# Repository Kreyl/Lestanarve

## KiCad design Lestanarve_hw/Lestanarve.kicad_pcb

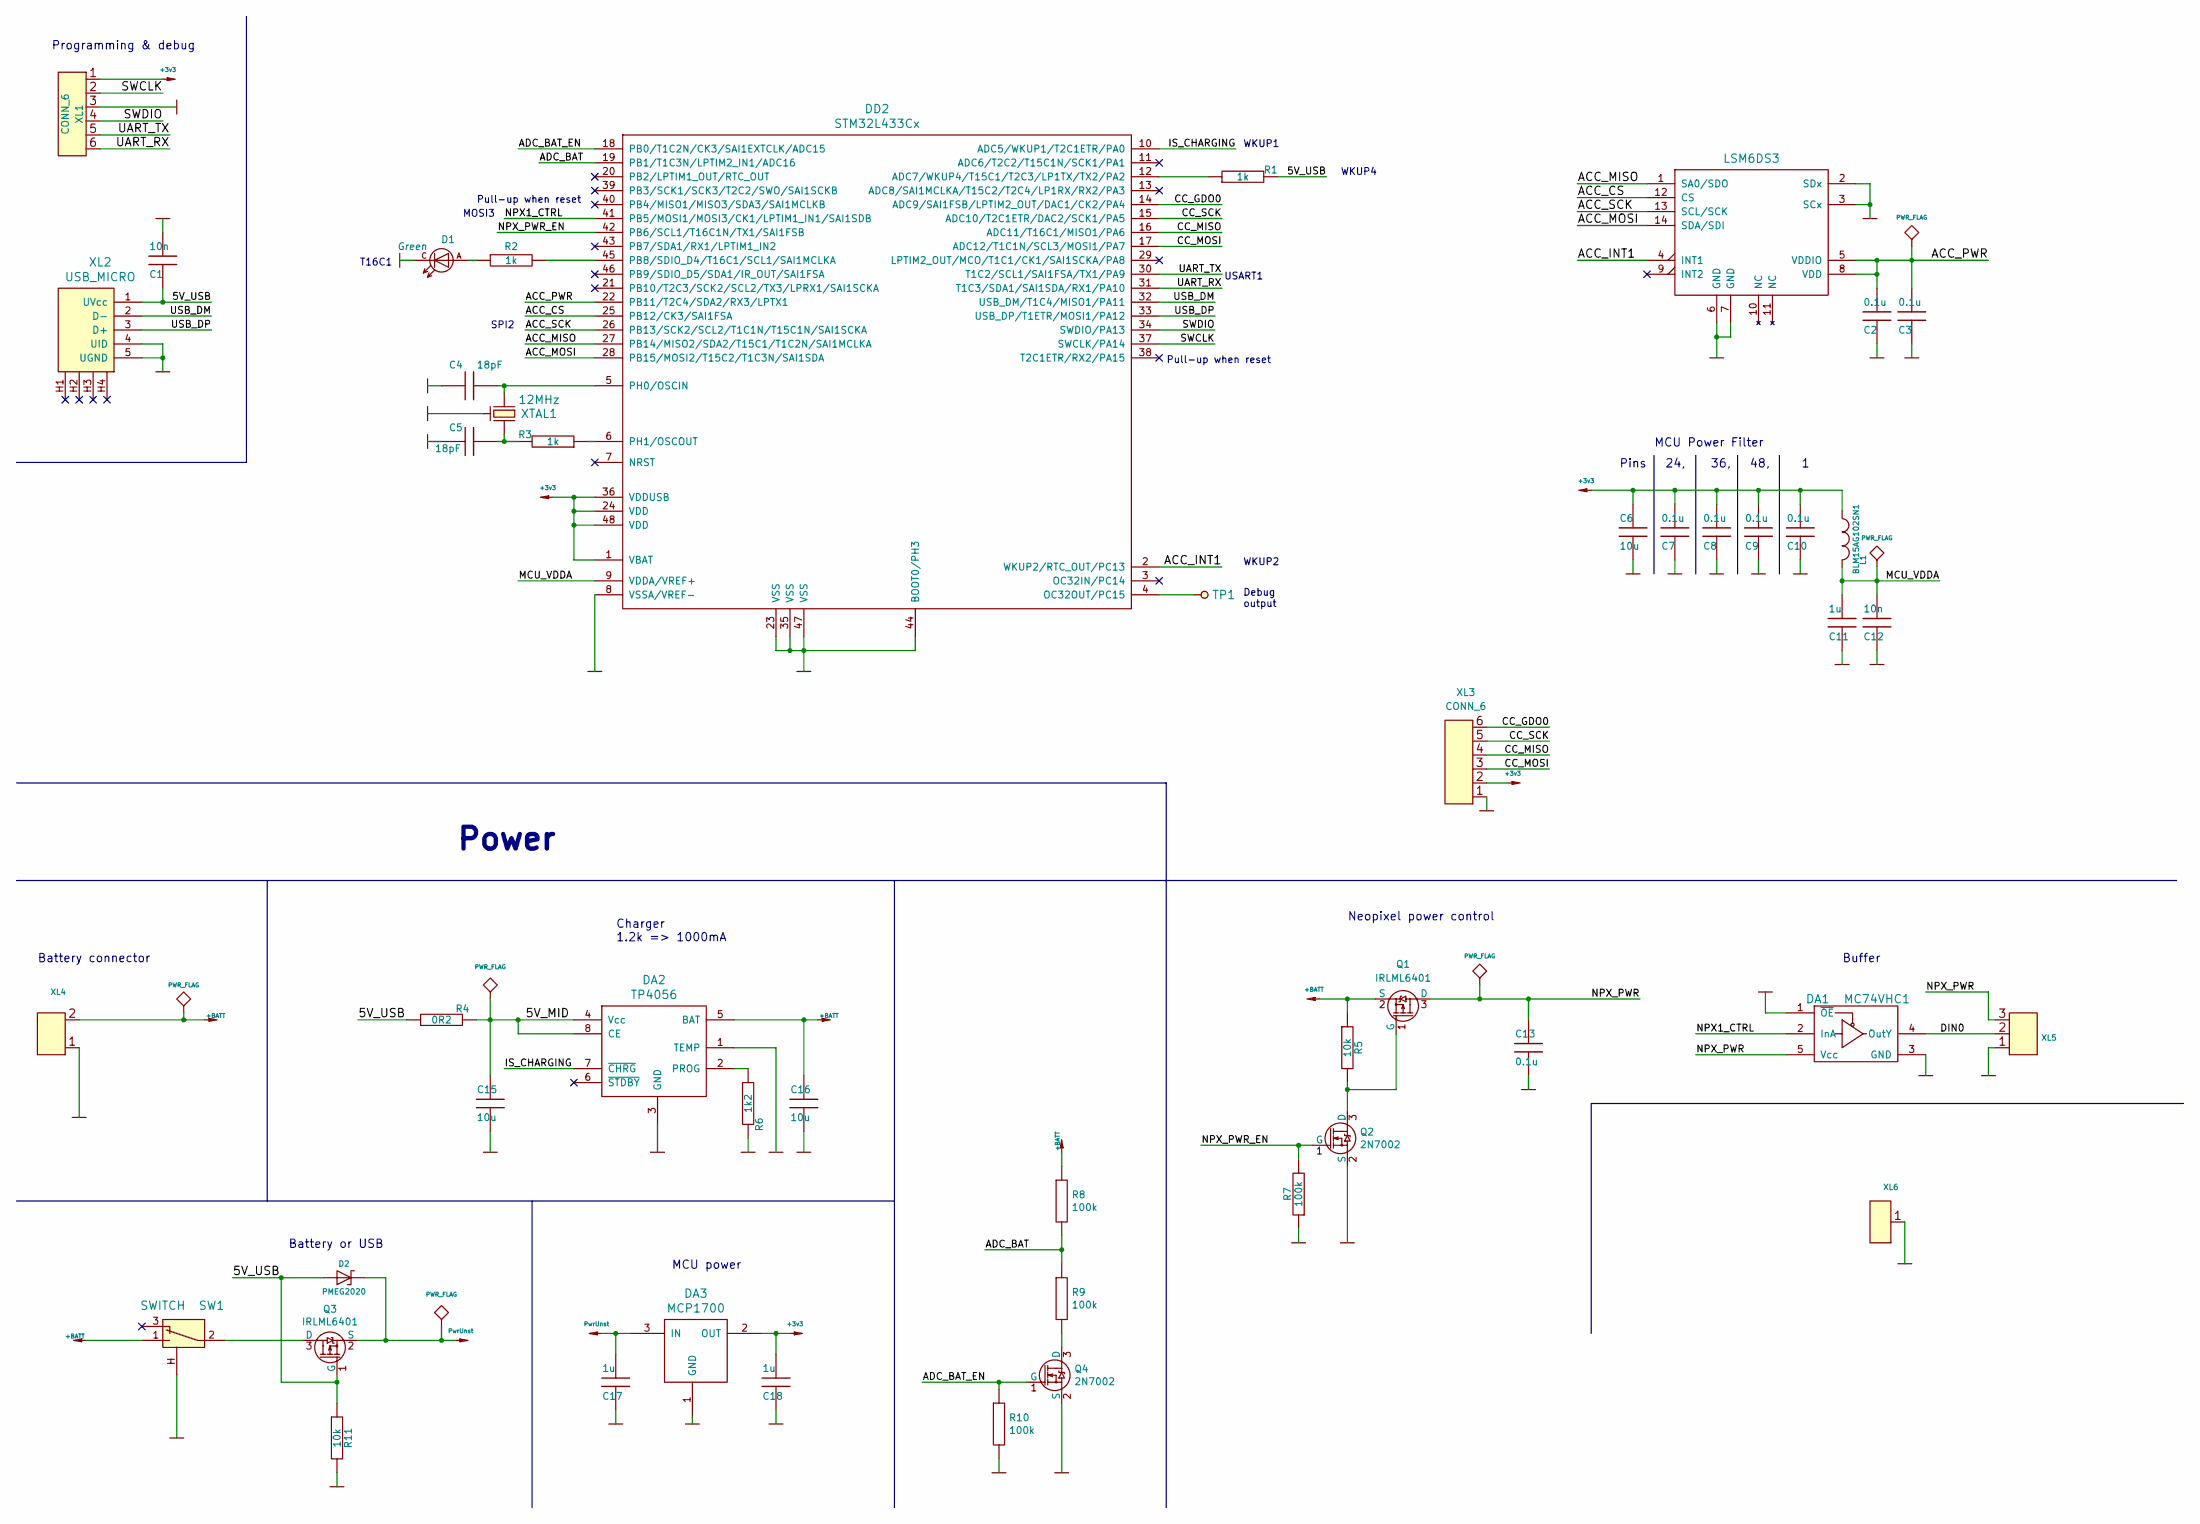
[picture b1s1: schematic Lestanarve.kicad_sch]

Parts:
C1, C12: 10n; CAP_0603_Silks
C2, C3, C7, C8, C9, C10, C13: 0.1u; CAP_0603_Silks
C4, C5: 18pF; CAP_0603_Silks
C6, C15, C16: 10u; CAP_0603_Silks
C11, C17, C18: 1u; CAP_0603_Silks
D1: LED; LED_0603_ch
D2: PMEG2020; SOD323
DA1: MC74VHC1; SOT23-5
DA2: TP4056; SO8_150MIL
DA3: MCP1700; SOT23-3A
DD1: LSM6DS3; 14_3x2d5_p0d5
DD2: STM32L433Cx; LQFP48
L1: BLM15AG102SN1; IND_0402; Tolerance 20%
Q1, Q3: IRLML6401; SOT23-3
Q2, Q4: 2N7002; SOT23-3
R1, R2, R3: 1k; RES_0603
R4: 0R2; RES_1206
R5, R11: 10k; RES_0603
R6: 1k2; RES_0603
R7, R8, R9, R10: 100k; RES_0603
SW1: SWITCH; SW_SS-1P2T_Housing
TP1: TESTPOINT; TESTPOINT_1MM
XL1: CONN_6; PLS-6_LOCK
XL2: USB_MICRO; USBmicro_MOLEX_1050170001
XL3: CONN_6; PLS-6-NoHole
XL4: CONN_2; WB-02R(MW-2MR)
XL5: CONN_3; WB-03(MW-3M)
XL6: CONN_1; PLS-1Square
XTAL1: 12MHz; 03225C4

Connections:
+3v3: C6.2, C7.1, C8.1, C9.1, C10.1, C18.1, DA3.2 (OUT), DD2.1 (VBAT), DD2.24 (VDD), DD2.36 (VDDUSB), DD2.48 (VDD), L1.1, XL1.1, XL3.2
+BATT: C16.2, DA2.5 (BAT), Q1.2 (S), R5.1, R8.1, SW1.1, XL4.2 (PM)
+PwrUnst: C17.1, D2.C, DA3.3 (IN), Q3.2 (S)
/5V_MID: C15.2, DA2.4 (Vcc), DA2.8 (CE), R4.2
/5V_USB: C1.2, D2.A, Q3.1 (G), R1.2, R4.1, R11.1, XL2.1 (UVcc)
/ACC_CS: DD1.12 (CS), DD2.25 (PB12/CK3/SAI1FSA)
/ACC_INT1: DD1.4 (INT1), DD2.2 (WKUP2/RTC_OUT/PC13)
/ACC_MISO: DD1.1 (SA0/SDO), DD2.27 (PB14/MISO2/SDA2/T15C1/T1C2N/SAI1MCLKA)
/ACC_MOSI: DD1.14 (SDA/SDI), DD2.28 (PB15/MOSI2/T15C2/T1C3N/SAI1SDA)
/ACC_PWR: C2.1, C3.1, DD1.5 (VDDIO), DD1.8 (VDD), DD2.22 (PB11/T2C4/SDA2/RX3/LPTX1)
/ACC_SCK: DD1.13 (SCL/SCK), DD2.26 (PB13/SCK2/SCL2/T1C1N/T15C1N/SAI1SCKA)
/ADC_BAT: DD2.19 (PB1/T1C3N/LPTIM2_IN1/ADC16), R8.2, R9.1
/ADC_BAT_EN: DD2.18 (PB0/T1C2N/CK3/SAI1EXTCLK/ADC15), Q4.1 (G), R10.1
/CC_GDO0: DD2.14 (ADC9/SAI1FSB/LPTIM2_OUT/DAC1/CK2/PA4), XL3.6
/CC_MISO: DD2.16 (ADC11/T16C1/MISO1/PA6), XL3.4
/CC_MOSI: DD2.17 (ADC12/T1C1N/SCL3/MOSI1/PA7), XL3.3
/CC_SCK: DD2.15 (ADC10/T2C1ETR/DAC2/SCK1/PA5), XL3.5
/DIN0: DA1.4 (OutY), XL5.2 (PM)
/IS_CHARGING: DA2.7 (~CHRG), DD2.10 (ADC5/WKUP1/T2C1ETR/PA0)
/MCU_VDDA: C11.1, C12.1, DD2.9 (VDDA/VREF+), L1.2
/NPX1_CTRL: DA1.2 (InA), DD2.41 (PB5/MOSI1/MOSI3/CK1/LPTIM1_IN1/SAI1SDB)
/NPX_PWR: C13.2, DA1.5 (Vcc), Q1.3 (D), XL5.3
/NPX_PWR_EN: DD2.42 (PB6/SCL1/T16C1N/TX1/SAI1FSB), Q2.1 (G), R7.2
/SWCLK: DD2.37 (SWCLK/PA14), XL1.2
/SWDIO: DD2.34 (SWDIO/PA13), XL1.4
/UART_RX: DD2.31 (T1C3/SDA1/SAI1SDA/RX1/PA10), XL1.6
/UART_TX: DD2.30 (T1C2/SCL1/SAI1FSA/TX1/PA9), XL1.5
/USB_DM: DD2.32 (USB_DM/T1C4/MISO1/PA11), XL2.2 (D-)
/USB_DP: DD2.33 (USB_DP/T1ETR/MOSI1/PA12), XL2.3 (D+)
GND: C1.1, C2.2, C3.2, C4.2, C5.2, C6.1, C7.2, C8.2, C9.2, C10.2, C11.2, C12.2, C13.1, C15.1, C16.1, C17.2, C18.2, D1.C, DA1.1 (~OE), DA1.3 (GND), DA2.1 (TEMP), DA2.3 (GND), DA3.1 (GND), DD1.2 (SDx), DD1.3 (SCx), DD1.6 (GND), DD1.7 (GND), DD2.8 (VSSA/VREF-), DD2.23 (VSS), DD2.35 (VSS), DD2.44 (BOOT0/PH3), DD2.47 (VSS), Q2.2 (S), Q4.2 (S), R6.2, R7.1, R10.2, R11.2, SW1.H, XL1.3, XL2.4 (UID), XL2.5 (UGND), XL3.1, XL4.1, XL5.1, XL6.1, XTAL1.H
unnamed: C4.1, DD2.5 (PH0/OSCIN), XTAL1.1
unnamed: C5.1, R3.2, XTAL1.2
unnamed: D1.A, R2.1
unnamed: DA2.2 (PROG), R6.1
unnamed: DD2.4 (OC32OUT/PC15), TP1.1
unnamed: DD2.6 (PH1/OSCOUT), R3.1
unnamed: DD2.12 (ADC7/WKUP4/T15C1/T2C3/LP1TX/TX2/PA2), R1.1
unnamed: DD2.45 (PB8/SDIO_D4/T16C1/SCL1/SAI1MCLKA), R2.2
unnamed: Q1.1 (G), Q2.3 (D), R5.2
unnamed: Q3.3 (D), SW1.2
unnamed: Q4.3 (D), R9.2

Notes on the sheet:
Pull-up when reset
WKUP4
Charger 1.2k => 1000mA
Pins 24, 36, 48, 1
SPI2
Debug output
Programming & debug
WKUP1
Battery or USB
Buffer
Power
MCU Power Filter
T16C1
WKUP2
Battery connector
MOSI3
USART1
Neopixel power control
MCU power

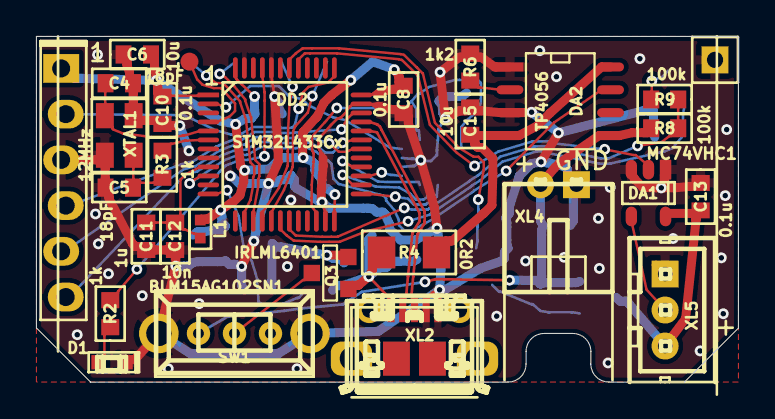
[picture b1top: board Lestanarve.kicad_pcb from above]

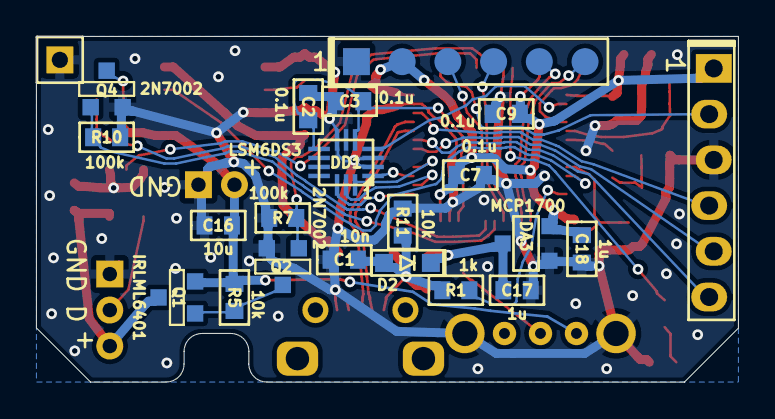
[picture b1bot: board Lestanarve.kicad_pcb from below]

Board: 2 copper layers, 39.0 x 19.2 mm, 49 parts (20 on the bottom side), 41 nets.

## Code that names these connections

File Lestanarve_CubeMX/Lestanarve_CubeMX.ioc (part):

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Mcu.Name=STM32L433C(B-C)Tx
Mcu.Package=LQFP48
Mcu.UserName=STM32L433CBTx
PA10.Mode=Asynchronous
PA10.Signal=USART1_RX
PA11.Mode=Device
PA11.Signal=USB_DM
PA12.Mode=Device
PA12.Signal=USB_DP
PA13\ (JTMS-SWDIO).Mode=Serial_Wire
PA13\ (JTMS-SWDIO).Signal=SYS_JTMS-SWDIO
PA14\ (JTCK-SWCLK).Mode=Serial_Wire
PA14\ (JTCK-SWCLK).Signal=SYS_JTCK-SWCLK
PA2.Mode=SYS_WakeUp3
PA2.Signal=SYS_WKUP4
PA9.Mode=Asynchronous
PA9.Signal=USART1_TX
PB1.Signal=ADCx_IN16
PB10.Mode=Full_Duplex_Master
PB10.Signal=SPI2_SCK
PB14.Mode=Full_Duplex_Master
PB14.Signal=SPI2_MISO
PB15.Mode=Full_Duplex_Master
PB15.Signal=SPI2_MOSI
PB3\ (JTDO-TRACESWO).Mode=TX_Only_Simplex_Unidirect_Master
PB3\ (JTDO-TRACESWO).Signal=SPI3_SCK
PB5.Mode=TX_Only_Simplex_Unidirect_Master
PB5.Signal=SPI3_MOSI
PC13.Mode=SYS_WakeUp1
PC13.Signal=SYS_WKUP2
PH0-OSC_IN\ (PH0).Mode=HSE-External-Oscillator
PH0-OSC_IN\ (PH0).Signal=RCC_OSC_IN
PH1-OSC_OUT\ (PH1).Mode=HSE-External-Oscillator
PH1-OSC_OUT\ (PH1).Signal=RCC_OSC_OUT
RCC.HSE_VALUE=12000000
RCC.SYSCLKFreq_VALUE=40000000
RCC.SYSCLKSource=RCC_SYSCLKSOURCE_PLLCLK
board=custom

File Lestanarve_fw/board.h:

#pragma once

// ==== General ====
#define APP_NAME            "Lestanarve"

#ifndef TRUE
#define TRUE 1
#endif

// Version of PCB
#define PCB_VER                 1

// MCU type as defined in the ST header.
#define STM32L433xx

// Freq of external crystal if any. Leave it here even if not used.
#define CRYSTAL_FREQ_HZ         12000000

// OS timer settings
#define STM32_ST_IRQ_PRIORITY   2
#define STM32_ST_USE_TIMER      2
#define SYS_TIM_CLK             (Clk.APB1FreqHz)    // Timer 5 is clocked by APB1

//  Periphery
#define I2C1_ENABLED            FALSE
#define I2C2_ENABLED            FALSE
#define I2C3_ENABLED            FALSE
#define SIMPLESENSORS_ENABLED   TRUE
#define BUTTONS_ENABLED         FALSE

#define ADC_REQUIRED            TRUE
#define STM32_DMA_REQUIRED      TRUE    // Leave this macro name for OS

#if 1 // ========================== GPIO =======================================
// EXTI
#define INDIVIDUAL_EXTI_IRQ_REQUIRED    FALSE

// Buttons
#define BTN1_PIN        GPIOA, 0

// Battery
#define IS_CHARGING     GPIOA, 0, pudPullUp
#define BAT_MEAS_EN     GPIOB, 0
#define BAT_ADC_PIN     GPIOB, 1, 16 // PB1, ADC channel 16

// Light
#define LED_PIN         { GPIOB, 8, TIM16, 1, invNotInverted, omPushPull, 255 }
// Npx LEDs
#define NPX_LED_CNT     28
#define NPX_SPI         SPI3
#define NPX_DATA_PIN    GPIOB, 5, AF6
#define NPX_PWR_PIN     GPIOB, 6

// USB
#define USB_DM          GPIOA, 11
#define USB_DP          GPIOA, 12
#define USB_AF          AF10
#define USB_DETECT_PIN  GPIOA, 2

// Radio: SPI, PGpio, Sck, Miso, Mosi, Cs, Gdo0
#define CC_Setup0       SPI1, GPIOA, 5,6,7, GPIOC,15, GPIOA,4

// UART
#define UART_GPIO       GPIOA
#define UART_TX_PIN     9
#define UART_RX_PIN     10

// Acc
#define ACG_IRQ_PIN     GPIOC, 13
#define ACG_CS_PIN      GPIOB, 12
#define ACG_SCK_PIN     GPIOB, 13, omPushPull, pudNone, AF5
#define ACG_MISO_PIN    GPIOB, 14, omPushPull, pudNone, AF5
#define ACG_MOSI_PIN    GPIOB, 15, omPushPull, pudNone, AF5
#define ACG_PWR_PIN     GPIOB, 11
#define ACG_SPI         SPI2

// I2C
#define I2C1_GPIO       GPIOB
#define I2C1_SCL        8
#define I2C1_SDA        9
// I2C Alternate Function
#define I2C_AF          AF4

#endif // GPIO

#if 1 // =========================== I2C =======================================
// i2cclkPCLK1, i2cclkSYSCLK, i2cclkHSI
#define I2C_CLK_SRC     i2cclkHSI
#define I2C_BAUDRATE_HZ 400000
#endif

#if ADC_REQUIRED // ======================= Inner ADC ==========================
// Clock divider: clock is generated from the APB2
#define ADC_CLK_DIVIDER		adcDiv2

// ADC channels
#define ADC_BATTERY_CHNL 	14
// ADC_VREFINT_CHNL
#define ADC_CHANNELS        { ADC_BATTERY_CHNL, ADC_VREFINT_CHNL }
#define ADC_CHANNEL_CNT     2   // Do not use countof(AdcChannels) as preprocessor does not know what is countof => cannot check
#define ADC_SAMPLE_TIME     ast24d5Cycles
#define ADC_OVERSAMPLING_RATIO  64   // 1 (no oversampling), 2, 4, 8, 16, 32, 64, 128, 256
#endif

#if 1 // =========================== DMA =======================================
// ==== Uart ====
// Remap is made automatically if required
#define UART_DMA_TX     STM32_DMA_STREAM_ID(2, 6)
#define UART_DMA_RX     STM32_DMA_STREAM_ID(2, 7)
#define UART_DMA_CHNL   2
#define UART_DMA_TX_MODE(Chnl) (STM32_DMA_CR_CHSEL(Chnl) | DMA_PRIORITY_LOW | STM32_DMA_CR_MSIZE_BYTE | STM32_DMA_CR_PSIZE_BYTE | STM32_DMA_CR_MINC | STM32_DMA_CR_DIR_M2P | STM32_DMA_CR_TCIE)
#define UART_DMA_RX_MODE(Chnl) (STM32_DMA_CR_CHSEL(Chnl) | DMA_PRIORITY_MEDIUM | STM32_DMA_CR_MSIZE_BYTE | STM32_DMA_CR_PSIZE_BYTE | STM32_DMA_CR_MINC | STM32_DMA_CR_DIR_P2M | STM32_DMA_CR_CIRC)

// ==== Npx ====
#define NPX_DMA         STM32_DMA_STREAM_ID(2, 2)  // SPI3 TX
#define NPX_DMA_REQ     3

// ==== ACG ====
#define ACG_DMA_TX      STM32_DMA_STREAM_ID(1, 5)
#define ACG_DMA_RX      STM32_DMA_STREAM_ID(1, 4)
#define ACG_DMA_CHNL    1

// ==== I2C ====
#define I2C1_DMA_TX     STM32_DMA_STREAM_ID(1, 6)
#define I2C1_DMA_RX     STM32_DMA_STREAM_ID(1, 7)
#define I2C1_DMA_CHNL   3

#if ADC_REQUIRED
#define ADC_DMA         STM32_DMA_STREAM_ID(1, 1)
#define ADC_DMA_MODE    STM32_DMA_CR_CHSEL(0) |   /* DMA1 Stream1 Channel0 */ \
                        DMA_PRIORITY_LOW | \
                        STM32_DMA_CR_MSIZE_HWORD | \
                        STM32_DMA_CR_PSIZE_HWORD | \
                        STM32_DMA_CR_MINC |       /* Memory pointer increase */ \
                        STM32_DMA_CR_DIR_P2M |    /* Direction is peripheral to memory */ \
                        STM32_DMA_CR_TCIE         /* Enable Transmission Complete IRQ */
#endif // ADC

#endif // DMA

#if 1 // ========================== USART ======================================
#define PRINTF_FLOAT_EN TRUE
#define UART_TXBUF_SZ   2048
#define UART_RXBUF_SZ   128
#define CMD_BUF_SZ      64

#define CMD_UART        USART1

#define CMD_UART_PARAMS \
    CMD_UART, UART_GPIO, UART_TX_PIN, UART_GPIO, UART_RX_PIN, \
    UART_DMA_TX, UART_DMA_RX, UART_DMA_TX_MODE(UART_DMA_CHNL), UART_DMA_RX_MODE(UART_DMA_CHNL), \
    uartclkHSI // Use independent clock

#endif

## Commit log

2021-12-13 Sch in progress
2021-12-24 + UART works
2021-12-25 + Led + NPXs work
2022-01-07 All low-level works
2022-01-29 + Lookup table + py conv + Eff radius & concentric
2022-01-30 + Stochastic effect ok
2022-01-30 + Acg controlled params
2022-01-31 USB and filesys integrated, but do not work
2022-02-02 + USB MSD works, disk formatted + Settings.ini constructed
2022-02-02 Working on settings
2022-02-03 +Settings + Settings load ok
2022-02-03 in progress
2022-02-04 Motion logic moved to dedicated file
2022-02-04 * 40 MHz USB and effects works ok
2022-02-04 + Charging indication
2022-02-05 + ADC RC
